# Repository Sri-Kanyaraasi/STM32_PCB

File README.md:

# STM32_PCB
PCB Designed using KiCad

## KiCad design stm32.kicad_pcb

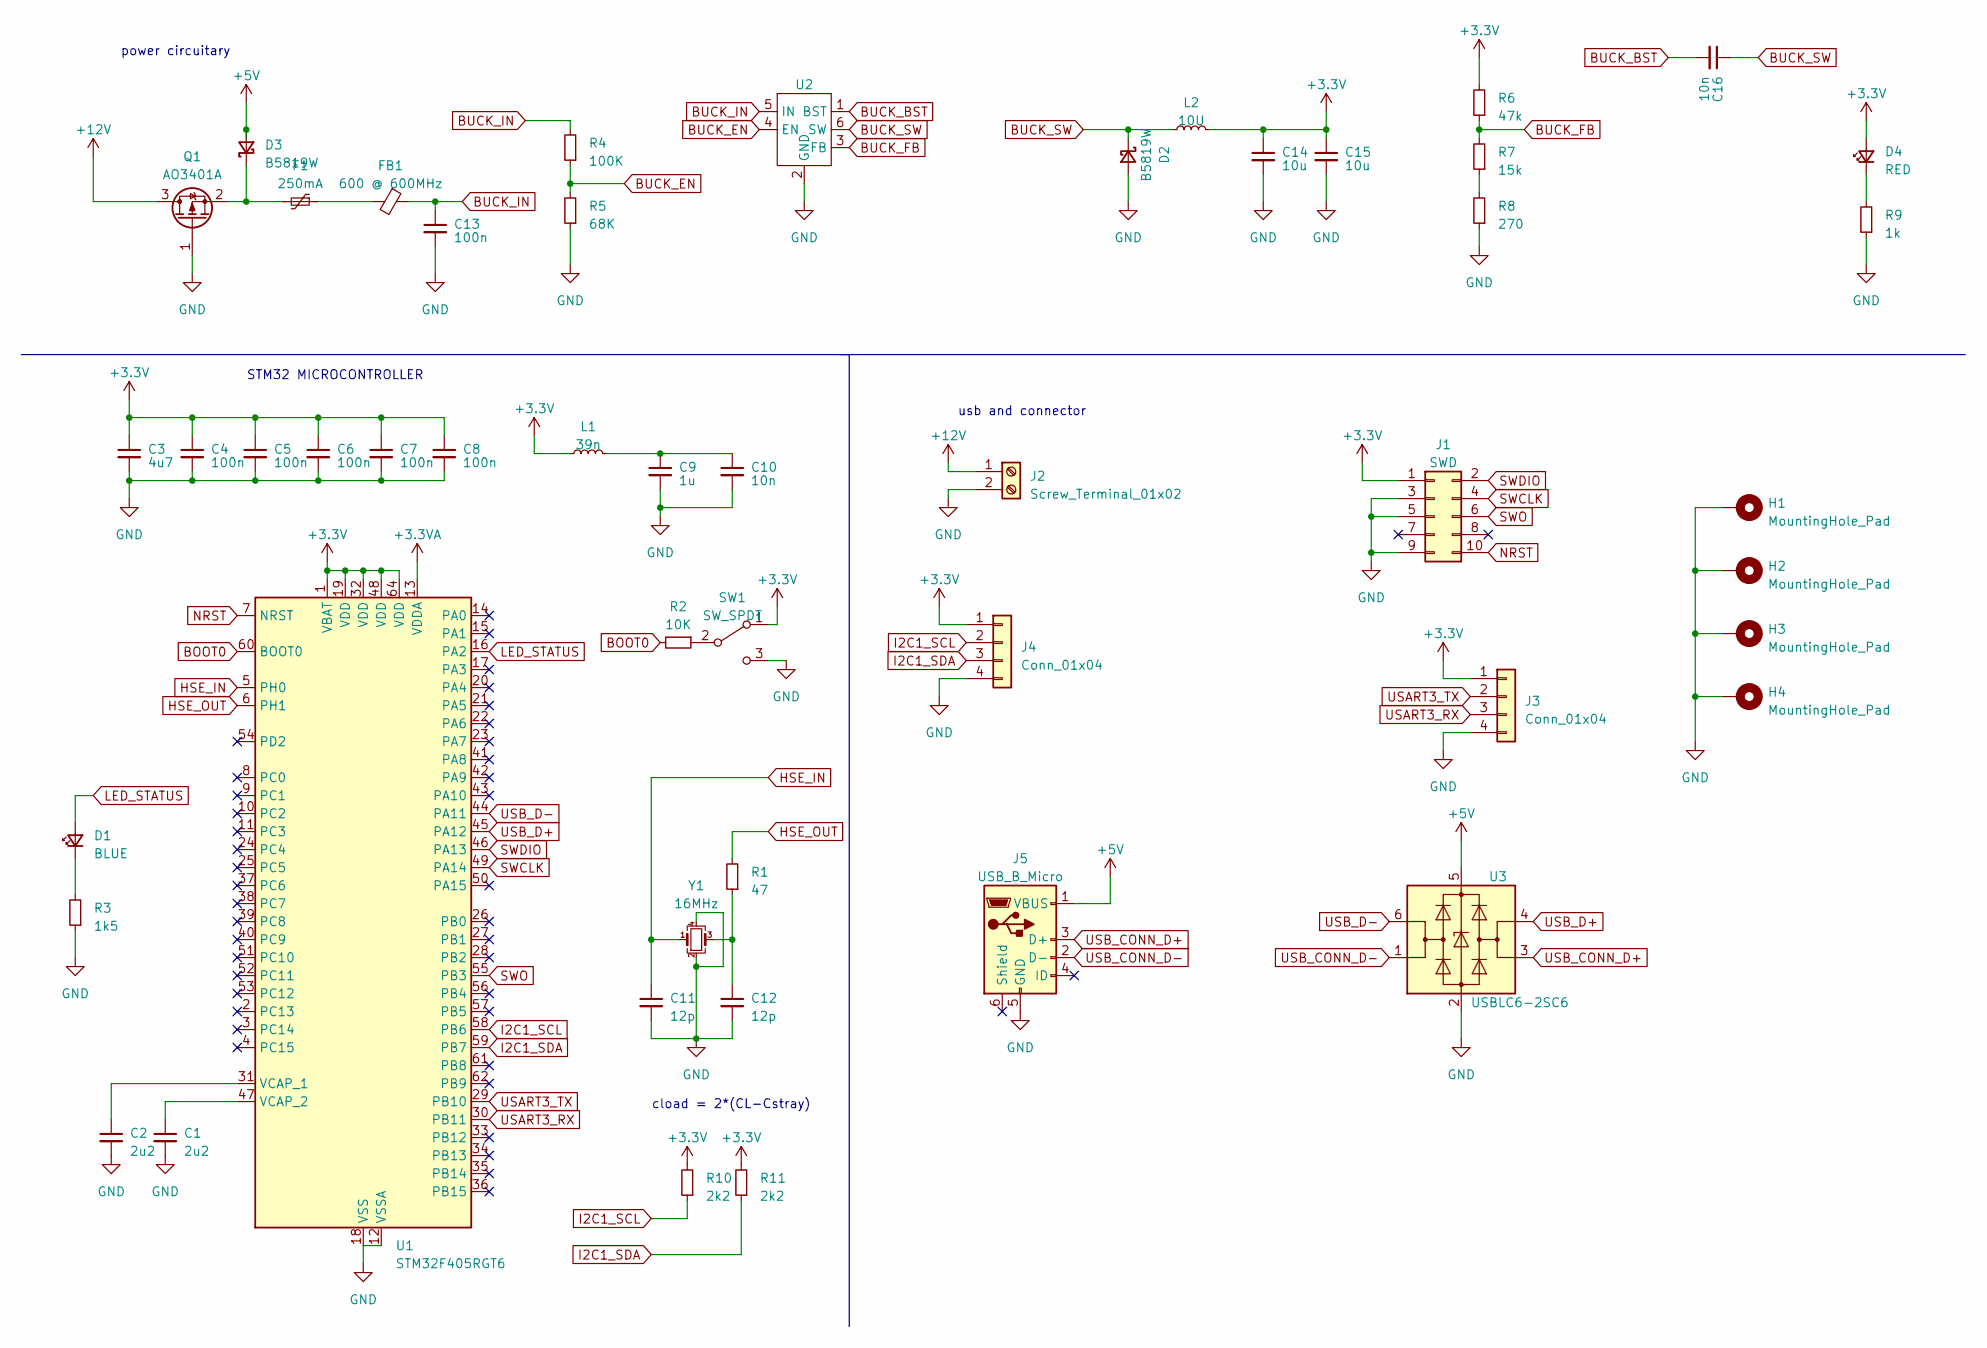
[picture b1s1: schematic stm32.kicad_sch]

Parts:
C1, C2: 2u2; C_0603_1608Metric
C3: 4u7; C_0603_1608Metric
C4, C5, C6, C7, C8: 100n; C_0402_1005Metric
C9: 1u; C_0402_1005Metric
C10: 10n; C_0603_1608Metric
C11, C12: 12p; C_0402_1005Metric
C13: 100n; C_1206_3216Metric
C14, C15: 10u; C_1206_3216Metric
C16: 10n; C_0402_1005Metric
D1: BLUE; LED_0603_1608Metric
D2, D3: B5819W; D_SOD-123
D4: RED; LED_0603_1608Metric
F1: 250mA; Fuse_1206_3216Metric
FB1: 600 @ 600MHz; L_0805_2012Metric
H1, H2, H3, H4: MountingHole_Pad; MountingHole_4.3mm_M4_Pad_Via
J1: SWD; PinSocket_2x05_P1.27mm_Vertical_SMD
J2: Screw_Terminal_01x02; TerminalBlock_Phoenix_PT-1,5-2-3.5-H_1x02_P3.50mm_Horizontal
J3, J4: Conn_01x04; Molex_PicoBlade_53048-0410_1x04_P1.25mm_Horizontal
J5: USB_B_Micro; AMPHENOL_10118193-0001LF
L1: 39n; L_0402_1005Metric
L2: 10U; L_Sunlord_MWSA0518S
Q1: AO3401A; SOT-23
R1: 47; R_0402_1005Metric
R2: 10K; R_0402_1005Metric
R3: 1k5; R_0603_1608Metric
R4: 100K; R_0603_1608Metric
R5: 68K; R_0603_1608Metric
R6: 47k; R_0603_1608Metric
R7: 15k; R_0603_1608Metric
R8: 270; R_0603_1608Metric
R9: 1k; R_0603_1608Metric
R10, R11: 2k2; R_0402_1005Metric
SW1: SW_SPDT; SW_SPDT_PCM12
U1: STM32F405RGT6; LQFP-64_10x10mm_P0.5mm
U2: SOT-23-6
U3: USBLC6-2SC6; SOT-23-6
Y1: 16MHz; Crystal_SMD_3225-4Pin_3.2x2.5mm

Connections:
+3.3V: C3.1, C4.1, C5.1, C6.1, C7.1, C8.1, C14.1, C15.1, D4.2 (A), J1.1, J3.1, J4.1, L1.1, L2.2, R6.2, R10.2, R11.2, SW1.1 (A), U1.1 (VBAT), U1.19 (VDD), U1.32 (VDD), U1.48 (VDD), U1.64 (VDD)
+3.3VA: U1.13 (VDDA)
+5V: D3.2 (A), J5.1 (VBUS), U3.5 (VBUS)
+12V: J2.1, Q1.3 (D)
BOOT0: R2.2, U1.60 (BOOT0)
BUCK_BST: C16.2, U2.1 (BST)
BUCK_EN: R4.1, R5.2, U2.4 (EN)
BUCK_FB: R6.1, R7.2, U2.3 (FB)
BUCK_IN: C13.1, FB1.1, R4.2, U2.5 (IN)
BUCK_SW: C16.1, D2.1 (K), L2.1, U2.6 (SW)
GND: C1.2, C2.2, C3.2, C4.2, C5.2, C6.2, C7.2, C8.2, C9.2, C10.2, C11.2, C12.2, C13.2, C14.2, C15.2, D2.2 (A), H1.1, H2.1, H3.1, H4.1, J1.3, J1.5, J1.9, J2.2, J3.4, J4.4, J5.5 (GND), Q1.1 (G), R3.1, R5.1, R8.1, R9.1, SW1.3 (C), U1.12 (VSSA), U1.18 (VSS), U1.63 (VSS), U2.2 (GND), U3.2 (GND), Y1.2, Y1.4
HSE_IN: C11.1, U1.5 (PH0), Y1.1
HSE_OUT: R1.2, U1.6 (PH1)
I2C1_SCL: J4.2, R10.1, U1.58 (PB6)
I2C1_SDA: J4.3, R11.1, U1.59 (PB7)
LED_STATUS: D1.2 (A), U1.16 (PA2)
NRST: J1.10, U1.7 (NRST)
unnamed: C9.1, C10.1, L1.2
unnamed: C12.1, R1.1, Y1.3
unnamed: D1.1 (K), R3.2
unnamed: D3.1 (K), F1.2, Q1.2 (S)
unnamed: D4.1 (K), R9.2
unnamed: F1.1, FB1.2
unnamed: R7.1, R8.2
unnamed: R2.1, SW1.2 (B)
unnamed: C2.1, U1.31 (VCAP_1)
unnamed: C1.1, U1.47 (VCAP_2)
SWCLK: J1.4, U1.49 (PA14)
SWDIO: J1.2, U1.46 (PA13)
SWO: J1.6, U1.55 (PB3)
USART3_RX: J3.3, U1.30 (PB11)
USART3_TX: J3.2, U1.29 (PB10)
USB_CONN_D+: J5.3 (D+), U3.3 (I/O2)
USB_CONN_D-: J5.2 (D-), U3.1 (I/O1)
USB_D+: U1.45 (PA12), U3.4 (I/O2)
USB_D-: U1.44 (PA11), U3.6 (I/O1)

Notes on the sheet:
usb and connector
STM32 MICROCONTROLLER
power circuitary
cload = 2*(CL-Cstray)

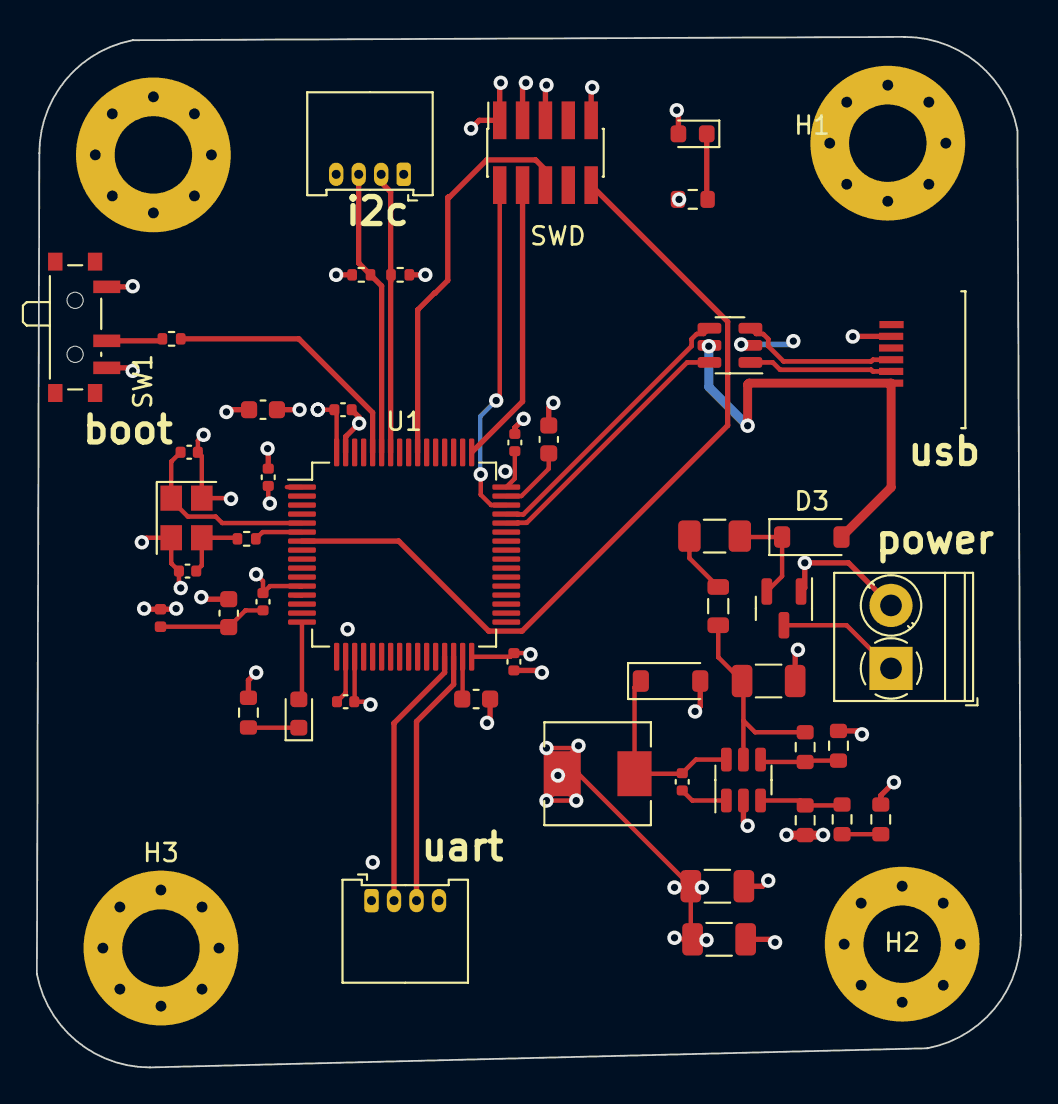
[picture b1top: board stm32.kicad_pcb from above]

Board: 4 copper layers, 54.7 x 57.3 mm, 50 parts (0 on the bottom side), 35 nets.
